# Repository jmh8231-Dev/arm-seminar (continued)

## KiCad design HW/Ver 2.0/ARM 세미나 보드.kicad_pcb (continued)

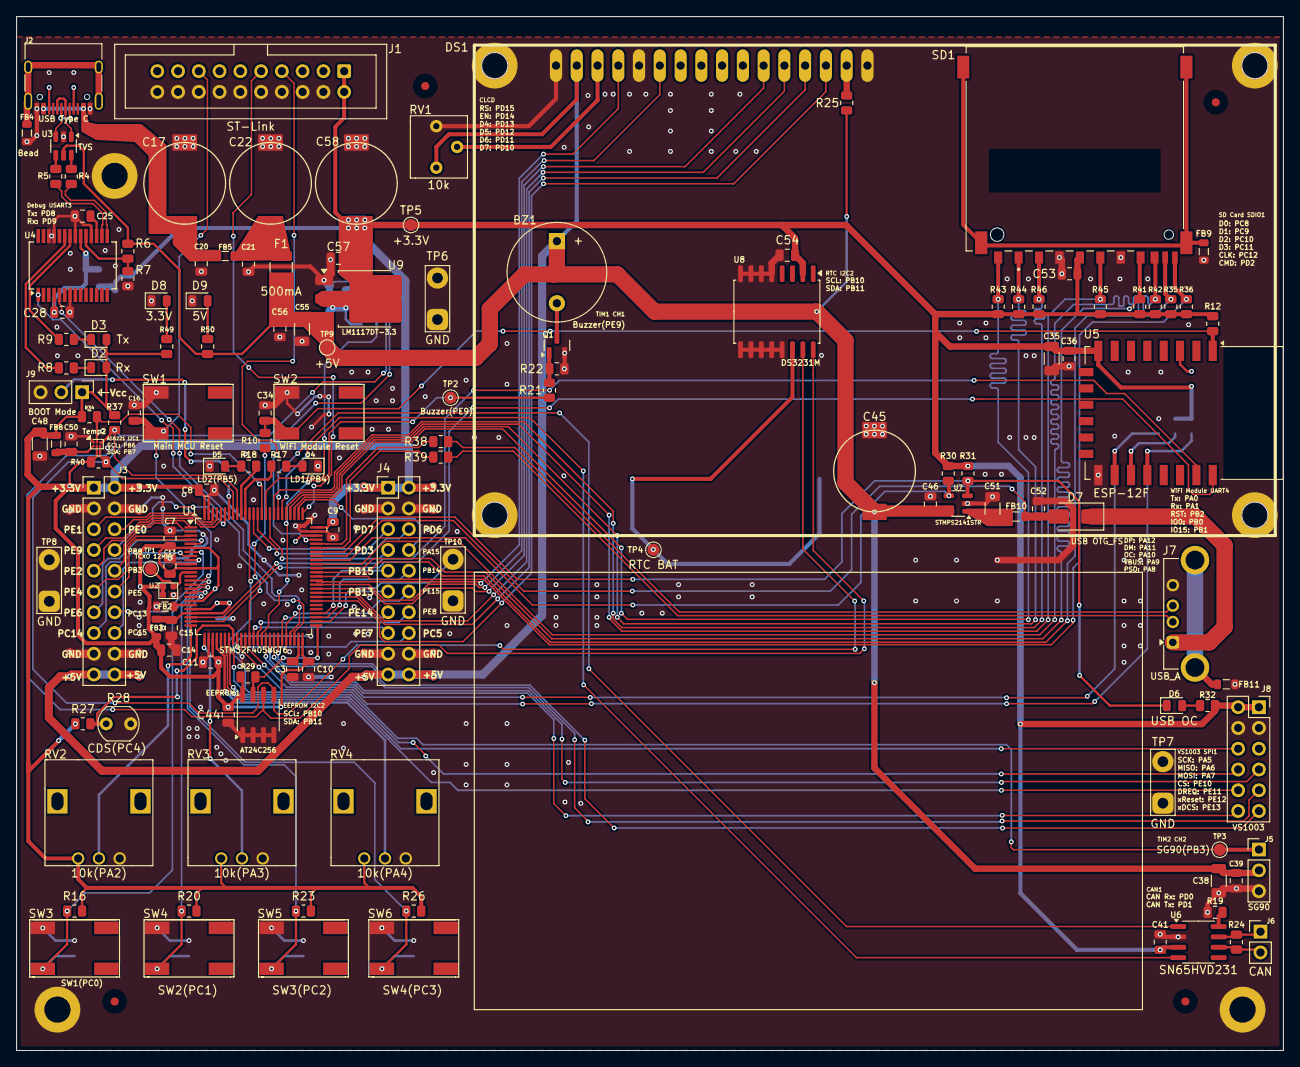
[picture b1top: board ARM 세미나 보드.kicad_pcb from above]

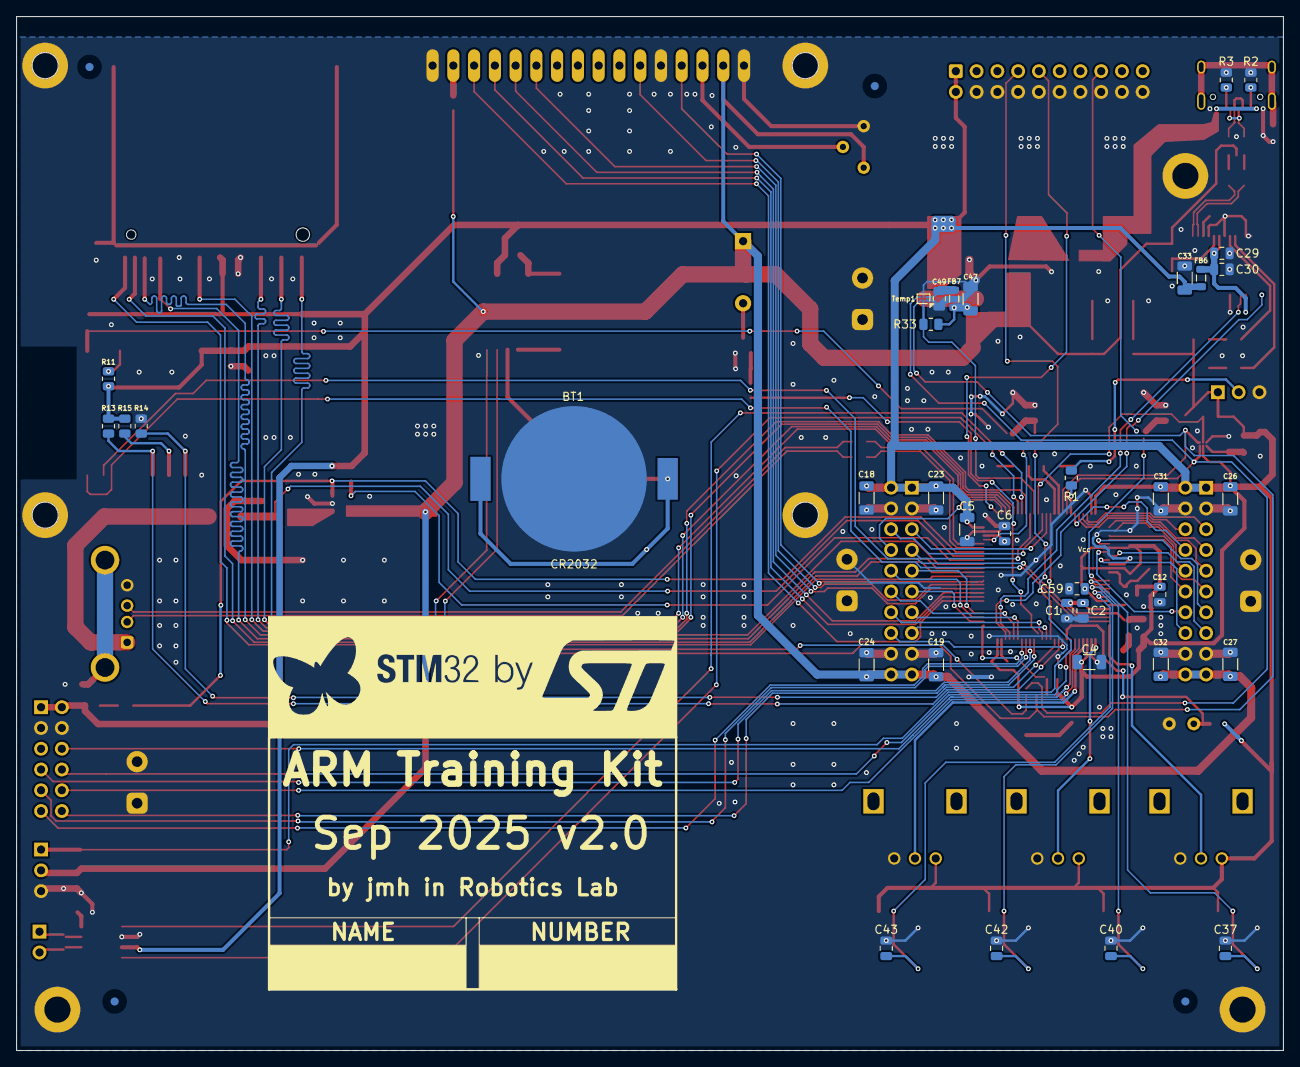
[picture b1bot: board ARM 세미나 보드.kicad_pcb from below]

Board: 2 copper layers, 155.0 x 126.5 mm, 172 parts (36 on the bottom side), 131 nets.

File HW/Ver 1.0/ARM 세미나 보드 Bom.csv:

"Reference","Qty","Value","DNP","Exclude from BOM","Exclude from Board","Footprint","Datasheet"
"BT1","1","CR2032","","","","PCB:BAT-HLD-001","~"
"BZ1","1","Buzzer(PE9)","","","","Buzzer_Beeper:Buzzer_12x9.5RM7.6","~"
"C1,C7,C8,C9,C10,C11,C12,C13,C16,C20,C21,C25,C28,C29,C34,C36,C37,C39,C40,C41,C42,C43,C44,C46,C49,C50,C52,C53,C54,C56,C57,C59","32","0.1uF","","","","Capacitor_SMD:C_0805_2012Metric","~"
"C2,C15","2","0.01uF","","","","Capacitor_SMD:C_0805_2012Metric","~"
"C3,C6","2","2.2uF","","","","Capacitor_SMD:C_0805_2012Metric","~"
"C4,C5,C18,C19,C23,C24,C26,C27,C31,C32,C33,C35,C38,C47,C48,C51,C55","17","10uF","","","","Capacitor_SMD:C_1206_3216Metric","~"
"C14","1","1uF","","","","Capacitor_SMD:C_0805_2012Metric","~"
"C17,C22,C45,C58","4","470uF","","","","PCB:MVG25WV470M","~"
"C30","1","4.7uF","","","","Capacitor_SMD:C_0805_2012Metric","~"
"D1,D7","2","M1","","","","Diode_SMD:D_SMA","~"
"D2","1","Rx","","","","LED_SMD:LED_0805_2012Metric","~"
"D3","1","Tx","","","","LED_SMD:LED_0805_2012Metric","~"
"D4","1","LD1(PB4)","","","","LED_SMD:LED_0805_2012Metric","~"
"D5","1","LD2(PB5)","","","","LED_SMD:LED_0805_2012Metric","~"
"D6","1","USB OC","","","","LED_SMD:LED_0805_2012Metric","~"
"D8","1","3.3V","","","","LED_SMD:LED_0805_2012Metric","~"
"D9","1","5V","","","","LED_SMD:LED_0805_2012Metric","~"
"DS1","1","CLCD 2004","","","","PCB:LCD-20x4","http://www.wincomlcd.com/pdf/WC1602A-SFYLYHTC06.pdf"
"EEPROM1","1","AT24C256","","","","Package_SO:SOIC-8_3.9x4.9mm_P1.27mm","https://www.onsemi.cn/PowerSolutions/document/CAT24C256-D.PDF"
"F1","1","500mA","","","","Inductor_SMD:L_1210_3225Metric","~"
"FB2,FB3,FB4,FB5,FB6,FB7,FB8,FB9,FB10,FB11","10","Bead","","","","Inductor_SMD:L_0805_2012Metric","~"
"J1","1","ST-Link","","","","Connector_IDC:IDC-Header_2x10_P2.54mm_Vertical","~"
"J2","1","USB Type C","","","","Connector_USB:USB_C_Receptacle_HRO_TYPE-C-31-M-12","https://www.usb.org/sites/default/files/documents/usb_type-c.zip"
"J3","1","PIN OUT A","","","","Connector_PinHeader_2.54mm:PinHeader_2x10_P2.54mm_Vertical","~"
"J4","1","PIN OUT B","","","","Connector_PinHeader_2.54mm:PinHeader_2x10_P2.54mm_Vertical","~"
"J5","1","SG90","","","","Connector_PinHeader_2.54mm:PinHeader_1x03_P2.54mm_Vertical","~"
"J6","1","CAN","","","","Connector_PinHeader_2.54mm:PinHeader_1x02_P2.54mm_Vertical","~"
"J7","1","USB_A","","","","Connector_USB:USB_A_Connfly_DS1095","~"
"J8","1","VS1003","","","","Connector_PinSocket_2.54mm:PinSocket_2x06_P2.54mm_Vertical","~"
"JP1","1","BOOT Mode","","","","Jumper:SolderJumper-3_P1.3mm_Open_RoundedPad1.0x1.5mm","~"
"Q1","1","BSS138","","","","Package_TO_SOT_SMD:SOT-23","https://www.onsemi.com/pub/Collateral/BSS138-D.PDF"
"R1,R7,R10,R11,R12,R13,R14,R15,R16,R19,R20,R23,R26,R27,R30,R33,R34,R35,R36,R41,R42,R43,R44,R45,R46,R50","26","10k","","","","Resistor_SMD:R_0805_2012Metric","~"
"R2,R3","2","5.1k","","","","Resistor_SMD:R_0805_2012Metric","~"
"R4,R5,R38,R39","4","22","","","","Resistor_SMD:R_0805_2012Metric","~"
"R6,R29,R37,R40,R47,R48","6","4.7k","","","","Resistor_SMD:R_0805_2012Metric","~"
"R8,R9,R17,R18,R22,R49","6","1k","","","","Resistor_SMD:R_0805_2012Metric","~"
"R21","1","220","","","","Resistor_SMD:R_0805_2012Metric","~"
"R24","1","120","","","","Resistor_SMD:R_0805_2012Metric","~"
"R25","1","330","","","","Resistor_SMD:R_0805_2012Metric","~"
"R28","1","CDS(PC4)","","","","OptoDevice:R_LDR_5.0x4.1mm_P3mm_Vertical","~"
"R31","1","47k","","","","Resistor_SMD:R_0805_2012Metric","~"
"R32","1","620","","","","Resistor_SMD:R_0805_2012Metric","~"
"RV1","1","10k","","","","PCB:3362P-103LF","~"
"RV2","1","10k(PA2)","","","","PCB:RV09H20SQ-B10K","~"
"RV3","1","10k(PA3)","","","","PCB:RV09H20SQ-B10K","~"
"RV4","1","10k(PA4)","","","","PCB:RV09H20SQ-B10K","~"
"SD1","1","SD Card","","","","PCB:AMPHENOL_GSD090012SEU",""
"SW1","1","Main MCU Reset","","","","PCB:SW_SMD_IT-1107","~"
"SW2","1","WiFi Module Reset","","","","PCB:SW_SMD_IT-1107","~"
"SW3","1","SW1(PC0)","","","","PCB:SW_SMD_IT-1107","~"
"SW4","1","SW2(PC1)","","","","PCB:SW_SMD_IT-1107","~"
"SW5","1","SW3(PC2)","","","","PCB:SW_SMD_IT-1107","~"
"SW6","1","SW4(PC3)","","","","PCB:SW_SMD_IT-1107","~"
"Temp1,Temp2","2","AS6221","","","","Package_CSP:WLCSP-6_1.4x1.0mm_P0.4mm",""
"TP1","1","TCXO 12MHz","","","","TestPoint:TestPoint_Pad_D1.5mm","~"
"TP2","1","Buzzer(PE9)","","","","TestPoint:TestPoint_Pad_D1.5mm","~"
"TP3","1","SG90(PB3)","","","","TestPoint:TestPoint_Pad_D1.5mm","~"
"TP4","1","RTC BAT","","","","TestPoint:TestPoint_Pad_D1.5mm","~"
"TP5","1","+3.3V","","","","TestPoint:TestPoint_Pad_D1.5mm","~"
"TP6,TP7,TP8,TP10","4","GND","","","","TestPoint:TestPoint_2Pads_Pitch5.08mm_Drill1.3mm","~"
"TP9","1","+5V","","","","TestPoint:TestPoint_Pad_D1.5mm","~"
"TP11,TP12","2","GND","DNP","","기판에서 제외됨","TestPoint:TestPoint_2Pads_Pitch5.08mm_Drill1.3mm","~"
"U1","1","STM32F405VGT6","","","","Package_QFP:LQFP-100_14x14mm_P0.5mm","https://www.st.com/resource/en/datasheet/stm32f405vg.pdf"
"U2","1","12MHz","","","","PCB:ECS-TXO-2016",""
"U3","1","TVS","","","","Package_TO_SOT_SMD:SOT-23-6","https://www.we-online.com/components/products/datasheet/8240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"
"U4","1","FT232RL","","","","Package_SO:SSOP-28_5.3x10.2mm_P0.65mm","https://www.ftdichip.com/Support/Documents/DataSheets/ICs/DS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"
"U5","1","ESP-12F","","","","RF_Module:ESP-12E","http://wiki.ai-thinker.com/_media/esp8266/esp8266_series_mod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"
"U6","1","SN65HVD231","","","","Package_SO:SOIC-8_3.9x4.9mm_P1.27mm","http://www.ti.com/lit/ds/symlink/sn65hvd230.pdf"
"U7","1","STMPS2141STR","","","","Package_TO_SOT_SMD:SOT-23-5",""
"U8","1","DS3231M","","","","Package_SO:SOIC-16W_7.5x10.3mm_P1.27mm","http://datasheets.maximintegrated.com/en/ds/DS3231.pdf"
"U9","1","LM1117DT-3.3","","","","Package_TO_SOT_SMD:TO-252-3_TabPin2","http://www.ti.com/lit/ds/symlink/lm1117.pdf"

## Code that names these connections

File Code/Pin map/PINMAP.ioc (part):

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Mcu.Name=STM32F405VGTx
Mcu.Package=LQFP100
Mcu.UserName=STM32F405VGTx
PA0-WKUP.Mode=Asynchronous
PA0-WKUP.Signal=UART4_TX
PA1.Mode=Asynchronous
PA1.Signal=UART4_RX
PA10.GPIOParameters=GPIO_Label
PA10.GPIO_Label=OTG_FS_OC
PA10.Signal=GPIO_Input
PA11.Mode=Host_Only
PA11.Signal=USB_OTG_FS_DM
PA12.Mode=Host_Only
PA12.Signal=USB_OTG_FS_DP
PA13.Mode=Serial_Wire
PA13.Signal=SYS_JTMS-SWDIO
PA14.Mode=Serial_Wire
PA14.Signal=SYS_JTCK-SWCLK
PA2.Signal=ADCx_IN2
PA3.Signal=ADCx_IN3
PA4.Signal=ADCx_IN4
PA5.Mode=Full_Duplex_Master
PA5.Signal=SPI1_SCK
PA6.Mode=Full_Duplex_Master
PA6.Signal=SPI1_MISO
PA7.Mode=Full_Duplex_Master
PA7.Signal=SPI1_MOSI
PA8.GPIOParameters=GPIO_Label
PA8.GPIO_Label=OTG_FS_PSO
PA8.Signal=GPIO_Output
PA9.Mode=Activate_VBUS
PA9.Signal=USB_OTG_FS_VBUS
PB0.GPIOParameters=GPIO_Label
PB0.GPIO_Label=ESP8266_GPIO0
PB0.Signal=GPIO_Output
PB1.GPIOParameters=GPIO_Label
PB1.GPIO_Label=ESP8266_GPIO15
PB1.Signal=GPIO_Output
PB10.Mode=I2C
PB10.Signal=I2C2_SCL
PB11.Mode=I2C
PB11.Signal=I2C2_SDA
PB12.GPIOParameters=GPIO_Label
PB12.GPIO_Label=EEPROM_WP
PB12.Signal=GPIO_Output
PB2.GPIOParameters=GPIO_Label
PB2.GPIO_Label=WiFi_Module_Reset
PB2.Signal=GPIO_Output
PB3.Signal=S_TIM2_CH2
PB4.Signal=GPIO_Output
PB5.Signal=GPIO_Output
PB6.Mode=I2C
PB6.Signal=I2C1_SCL
PB7.Mode=I2C
PB7.Signal=I2C1_SDA
PC0.Signal=GPXTI0
PC1.Signal=GPXTI1
PC10.Mode=SD_4_bits_Wide_bus
PC10.Signal=SDIO_D2
PC11.Mode=SD_4_bits_Wide_bus
PC11.Signal=SDIO_D3
PC12.Mode=SD_4_bits_Wide_bus
PC12.Signal=SDIO_CK
PC2.Signal=GPXTI2
PC3.Signal=GPXTI3
PC4.Signal=ADCx_IN14
PC6.GPIOParameters=GPIO_Label
PC6.GPIO_Label=SDIO_WP
PC6.Signal=GPIO_Input
PC7.GPIOParameters=GPIO_Label
PC7.GPIO_Label=SDIO_INT
PC7.Signal=GPXTI7
PC8.Mode=SD_4_bits_Wide_bus
PC8.Signal=SDIO_D0
PC9.Mode=SD_4_bits_Wide_bus
PC9.Signal=SDIO_D1
PD0.Mode=CAN_Activate
PD0.Signal=CAN1_RX
PD1.Mode=CAN_Activate
PD1.Signal=CAN1_TX
PD10.Signal=GPIO_Output
PD11.Signal=GPIO_Output
PD12.Signal=GPIO_Output
PD13.Signal=GPIO_Output
PD14.Signal=GPIO_Output
PD15.Signal=GPIO_Output
PD2.Mode=SD_4_bits_Wide_bus
PD2.Signal=SDIO_CMD
PD4.GPIOParameters=GPIO_Label
PD4.GPIO_Label=AS6221_INT1
PD4.Signal=GPXTI4
PD5.GPIOParameters=GPIO_Label
PD5.GPIO_Label=AS6221_INT2
PD5.Signal=GPXTI5
PD8.Mode=Asynchronous
PD8.Signal=USART3_TX
PD9.Mode=Asynchronous
PD9.Signal=USART3_RX
PE10.GPIOParameters=GPIO_Label
PE10.GPIO_Label=VS1003_CS
PE10.Signal=GPIO_Output
PE11.GPIOParameters=GPIO_Label
PE11.GPIO_Label=VS1003_DREQ
PE11.Signal=GPIO_Input
PE12.GPIOParameters=GPIO_Label
PE12.GPIO_Label=VS1003_xRESET
PE12.Signal=GPIO_Output
PE13.GPIOParameters=GPIO_Label
PE13.GPIO_Label=VS1003_xDCS
PE13.Signal=GPIO_Output
PE9.Signal=S_TIM1_CH1
PH0-OSC_IN.Mode=HSE-External-Oscillator
PH0-OSC_IN.Signal=RCC_OSC_IN
PH1-OSC_OUT.Mode=HSE-External-Oscillator
PH1-OSC_OUT.Signal=RCC_OSC_OUT
RCC.HSE_VALUE=12000000
RCC.SYSCLKFreq_VALUE=168000000
RCC.SYSCLKSource=RCC_SYSCLKSOURCE_PLLCLK
board=custom

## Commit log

2025-09-07 add file
2025-09-07 del file
2025-09-17 add HW v2.0
2025-11-05 add lib
2025-11-05 add doc
2025-11-13 addfile
2025-12-04 add chap 6
2025-12-04 add chap 6 file
2025-12-04 add chap6 ppt
2026-01-09 add img
2026-01-09 edit file name
